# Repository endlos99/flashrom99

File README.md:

FlashROM 99
===========

The *TI 99/4A Flash ROM Cartridge*, or FlashROM 99 for short, is a cartridge
for the TI 99/4A home computer that allows for running ROM cartridge images
stored on an SD card.

The FlashROM 99 supports ROM-only images of up to 32K that use the
write-to-`>60xx` bank switching scheme.  It will not work with programs
using GROMs or CRU-based bank switching.  The cartridge does not require the
Peripheral Expansion Box and runs on both PAL and NTSC consoles.

The project homepage is hosted at [GitHub][1].

FlashROM 99 is released as Open Source Hardware under the
[CERN OHL license][4] and the [GNU GPL license][5].  Both hardware design
files and firmware sources are available on [GitHub][2].

Using the FlashROM 99
---------------------

Using the FlashROM 99 is simple and doesn't require and special hardware or
software.

To begin, copy up to 171 cartridge image files onto an SD or SDHC card.
Switch off the TI 99 and plug in the FlashROM 99, then insert the SD card
into the FlashROM 99.  Switch on the TI 99 and wait until the activity
indicator on the FlashROM 99 is no longer lit.

Press any key to bring up the TI menu screen.  You should see the list of
images found on the SD card.  If the SD card contains more than 8 images, a
`FLASHROM 99` entry is shown instead.  Selecting this entry starts an image
browser where you can page through the list of available images with `,`,
`.`, `SPACE`, and number keys.

Select the image you want to run.  The screen will show a loader animation
while the image loads.  Once the image has been loaded, it will run
automatically.  The SD card is now no longer required and may be removed.

If only one image is found on the SD card, it is loaded immediately without
the need to select it first.

If you want to run a different program from the SD card, reset the TI 99 by
pressing `FCTN-=` and then reset the FlashROM 99 by pushing the reset
button.  If you do not reset the FlashROM 99, the TI menu will show only the
previously selected image.  Alternatively, you can power cycle the console,
which will reset both TI 99 and FlashROM 99.

For detailed usage information please refer to the [FlashROM 99 homepage][1].

Building the FlashROM 99
------------------------

The [GitHub repository][2] contains all hardware design files and software
sources required to build the FlashROM 99.

### Hardware

To assemble the FlashROM 99 you need the following components:

- 1x FlashROM 99 board
- 1x ATmega 8515 (either 8515-16 or 8515L-8)
- 1x 62256 32K SRAM (any speed rating)
- 1x 74HCT377 (LS may also work, but untested)
- 3x 74HCT541 (LS may also work, but untested)
- 6x 100 nF capacitors (e.g., multi-layer ceramic X7R, no electrolytic!)
- 1x 68 Ohm resistor
- 1x 330-470 Ohm resistor (depending on LED used, smaller values will be
     brighter)
- 1x 10 kOhm resistor
- 1x LED (e.g., 5 mm red or yellow)
- 1x micro push button
- 1x SD card module

The FlashROM 99 board was designed with [KiCad][6], a cross platform and
open source electronics design automation suite.  The design files are
stored in `pcb/`.

To simplify the board layout, the design uses an inexpensive SD module that
is readily available online.  Searching for `SD card Arduino` should give
you plenty of hits, including Amazon, ebay, and Pollin.  Make sure to pick a
module that matches the pin-out of the reference module shown below. Note
that the 3.3V input is not used, so any substitutes must be powered by 5V.

You can use any kind of single color LED, but you may have to adjust the 470
Ohm resistor if you choose anything other than red or yellow.

The push button is used to reset the board and will be pushed frequently.
You might choose an angled button if you prefer to push horizontally instead
of vertically.  This will also put less stress on the cart connector.

If the board shows connectors for a 1 nF capacitor next to the 377, do *not*
put this capacitor there, but leave the connectors empty.

When assembling the board make sure to place all ICs properly oriented --
some ICs are upside down!  On the board, the location of pin 1 is indicated
by a small line in the IC outline.  Socketing the ATmega allows for future
software updates.  It is best not to socket the 541s, however, as this will
make inserting the assembled cart into the TI 99 more difficult.

The push button is best soldered to the top of the board so that the bottom
area remains as smooth as possible.  After the button is soldered, put some
insulating tape on its bottom contacts to avoid interference with the SD
module.

Insert the SD module from the bottom and solder either one row of connectors
top so that the metal part of the module is flush with the board.  Some SD
modules have a crooked connector, though, so that a small gap may remain.

If you don't want to build the board yourself feel free to contact the
developer for available sources.

#### Previous Versions

Early versions of the FlashROM 99 used an additional 1 nF capacitor that
resulted in unreliable disk access on some, but not all systems with certain
disk controllers.

Please check to see if the 1 nF capacitor is present on your board.  If so,
simply remove it by desoldering or clipping its wires to improve the
stability of your cart.

If you applied a so-called "disk fix" to your board in the past, you don't
need to undo those changes when removing the capacitor.

### Software

The software for the ATmega 8515 consists of two components.  The `avr/`
folder contains the microcontroller logic for accessing the SD card, filling
the SRAM chip, and controlling the TI bus.

The `ti/` folder contains TI 99 assembly sources for the image menu and the
image browser.  The assembled TMS 9900 machine code is embedded in the
microcontroller code and loaded into RAM during operation.

To build the software, you first need to assemble the menu and browser
program with [`xas99`][3] and convert the generated machine code into C
code:

	$ cd ti/
	$ xas99.py -b -R -I <xdt99>/lib menu.a99
	$ mkmenu.py

Now you can compile the microcontroller code in `avr/`.  The folder contains
a `Makefile` for `avr-gcc` that will make compilation trivial.

	$ cd avr/
	$ make

As an option, you can enable multi-file functionality in the `Makefile`.
This feature, however, will severely extend the scan time for SD cards with
many images.  Only enable multi-file if you plan to use the FlashROM 99 with
no more than about two dozenzs of images per SD card.  To compile with
multi-file, you may have to disable FAT16 support in `avr/lib/pffconf.h` in
case the executable gets too large.

The build yields a `.hex` file that you can flash to the ATmega 8515 using
[`avrdude`][7] or your programmer of choice:

	$ avrdude -p atmega8515 -P /dev/ttyACM0 -c stk500 -U flash:w:flashrom99.hex

Additionally, you need to program the lower fuse bits of the 8515 so that it
runs at 8 MHz:

	$ avrdude -p atmega8515 -P /dev/ttyACM0 -c stk500 -U lfuse:w:0xe4:m

If you're using a different tool chain make sure to set `CKSEL3..0` in the
lower fuse byte to `0100`.  (Note that `0` means "programmed", and `1` means
"unprogrammed").  You can verfify that you're running at the right clock
speed by resetting the FlashROM 99 with no SD card inserted: The LED should
blink about once per second.

Finally, make sure that the bootloader is disabled by checking if higher
fuse bits `BOOTSZ1`, `BOOTSZ0`, and `BOOTRSET` are all set to `1`.  This
should be the default for new 8515s.

In the end, the lower and higher fuse bytes should have values `E4` and
`D9`, respectively.

About the Project
-----------------

The TI 99/4A Flash ROM Cartridge is Open Source Hardware released under the
[CERN OHL license][4], in the hope that TI 99 enthusiasts may find it useful.
Software components are released under the [GNU GPL license][5].

The hardware was designed with the open source electronics design automation
suite [KiCad][6].  The microcontroller code uses a modified version of the
[Petit FatFs][8] library.  Thanks go to Jon Guidry (acadiel) of `hexbus.com`
for designing the original bank switching circuitry for the first TI
multi-carts.

Contributions to both hardware and software are very welcome!  Please email
feedback, support questions, inquiries for parts, and bug reports to the
developer at <r@0x01.de>.  Discussions about the FlashROM 99 happen over at
[AtariAge][9].

[1]: https://endlos99.github.io/flashrom99
[2]: https://github.com/endlos99/flashrom99
[3]: https://endlos99.github.io/xdt99
[4]: http://www.ohwr.org/projects/cernohl/wiki
[5]: http://www.gnu.org/licenses/gpl.html
[6]: http://kicad.org
[7]: http://www.nongnu.org/avrdude/
[8]: http://elm-chan.org/fsw/ff/00index_p.html
[9]: http://atariage.com/forums/topic/250540-flash-rom-cart

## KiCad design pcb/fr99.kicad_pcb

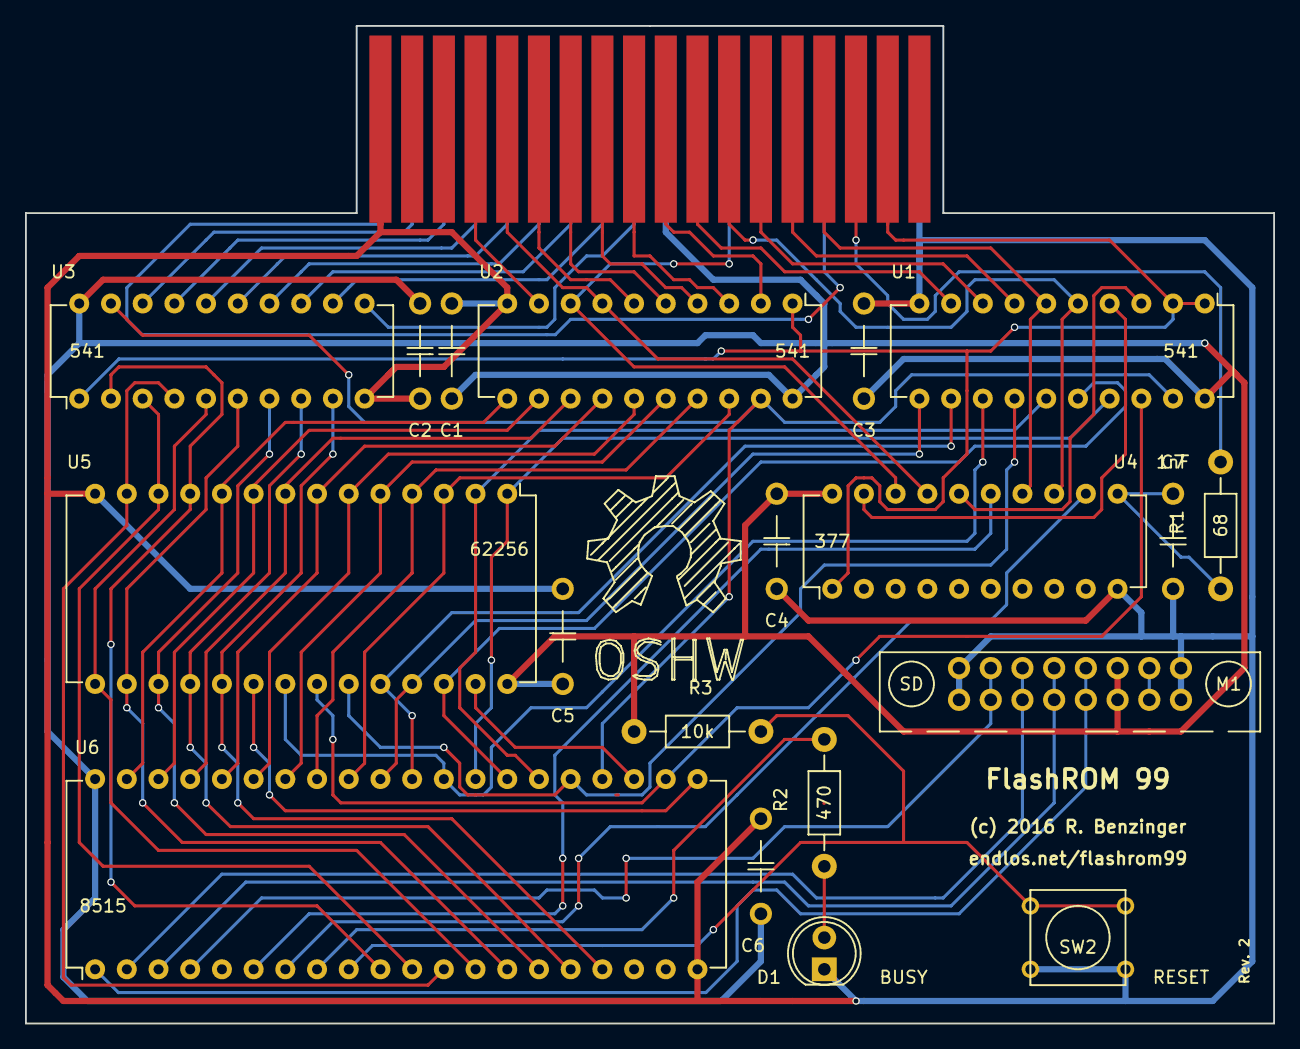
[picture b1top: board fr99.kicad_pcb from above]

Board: 2 copper layers, 100.0 x 79.9 mm, 20 parts (0 on the bottom side), 65 nets.

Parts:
C1, C2, C3, C4, C5, C6: 100nF; C_C
C7: 1nF; C_C
D1: BUSY; LED-5MM
M1: SD; SD_MODULE
P1: CONN_02X18; BUS_CART
R1: 68; Resistor_Horizontal_RM10mm
R2: 470; Resistor_Horizontal_RM10mm
R3: 10k; Resistor_Horizontal_RM10mm
SW2: RESET; SW_PUSH_SMALL
U1, U2, U3: 541; DIP-20_W7.62mm
U4: 377; DIP-20_W7.62mm
U5: 62256; DIP-28_W15.24mm
U6: 8515; DIP-40_W15.24mm

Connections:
+5V: C1.2, C2.2, C3.2, C4.2, C5.2, C6.2, M1.6, P1.19, R3.1, U1.20, U2.20, U3.20, U4.20, U5.28, U6.40
/A0: U2.11, U5.10, U6.39
/A1: U2.12, U5.9, U6.38
/A2: U2.13, U5.8, U6.37
/A3: U2.14, U5.7, U6.36
/A4: U2.15, U5.6, U6.35
/A5: U2.16, U5.5, U6.34
/A6: U2.17, U5.4, U6.33
/A7: U2.18, U5.3, U6.32
/A8: U1.11, U5.25, U6.31
/A9: U1.12, U5.24, U6.30
/A10: U1.13, U5.21, U6.29
/A11: U1.14, U5.23, U6.25
/A12: U1.15, U5.2, U6.26
/A13: U1.16, U5.26, U6.27
/A14: U1.17, U5.1, U6.28
/D0: U3.2, U5.11, U6.10
/D1: U3.3, U5.12, U6.11
/D2: U3.4, U5.13, U6.12
/D3: U3.5, U5.15, U6.13
/D4: U3.6, U5.16, U6.14
/D5: U3.7, U5.17, U6.15
/D6: U3.8, U5.18, U6.16
/D7: U3.9, U5.19, U6.17
BUSE: U1.19, U2.19, U3.19, U6.24
GND: C1.1, C2.1, C3.1, C4.1, C5.1, C6.1, C7.2, D1.1, M1.1, M1.8, P1.2, P1.35, SW2.1, U1.10, U2.10, U3.10, U4.10, U5.14, U6.20
unnamed: C7.1, R1.1, U4.11
unnamed: D1.2, R2.1
unnamed: M1.2, U6.4
unnamed: M1.3, U6.2
unnamed: M1.4, U6.3
unnamed: M1.5, U6.1
unnamed: P1.1, P1.29
unnamed: P1.3, U3.18
unnamed: P1.5, U3.17
unnamed: P1.7, U3.16
unnamed: P1.8, U2.9
unnamed: P1.9, U3.15
unnamed: P1.10, U2.7, U4.17
unnamed: P1.11, U3.14
unnamed: P1.12, U2.6
unnamed: P1.13, U3.13
unnamed: P1.14, U2.5
unnamed: P1.15, U3.12
unnamed: P1.16, U2.4
unnamed: P1.17, U3.11
unnamed: P1.18, U2.3
unnamed: P1.20, U2.2
unnamed: P1.22, U1.9
unnamed: P1.23, U2.8, U4.18
unnamed: P1.24, U1.5, U4.13
unnamed: P1.26, U1.8
unnamed: P1.28, U1.7
unnamed: P1.30, U1.6, U4.14
unnamed: P1.32, R1.2
unnamed: R2.2, U6.8
unnamed: R3.2, SW2.2, U6.9
unnamed: U1.3, U4.16
unnamed: U1.4, U4.19
unnamed: U1.18, U5.22, U6.22
unnamed: U4.12, U6.7
unnamed: U4.15, U6.6
unnamed: U5.20, U6.21
unnamed: U5.27, U6.23
ROMS: P1.34, U1.1, U1.2, U2.1, U3.1, U4.1

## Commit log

2016-05-07 FR99: documentation
2016-05-07 Create gh-pages branch via GitHub
2016-05-16 FR99: initial release of FlashROM 99 v1.0
2016-06-05 PCB: added values to silkscreen
2016-06-07 FR99: updated manual
2016-06-10 FR99: added sample images
2016-06-10 PCB: fixed bank switch (disk access issue)
2016-06-10 FR99: updated documentation
2016-06-12 FR99: clarified disk fix
2016-07-01 FR99: updated fix: no cap
2016-07-11 FR99: fixed typo in README
2016-09-15 FR99: removed obsolete disk fix images
2016-11-06 PCB: added Gerber files
2017-01-18 AVR: added HEX file
2018-04-16 DOC: fix fuse bytes description
2021-11-09 Update README.md
    https://forum.kicad.info/t/warning-avoid-all-links-to-kicad-pcb-org-use-kicad-org/31521

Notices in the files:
pcb/fr99.kicad_pcb:
Copyright (c) 2016 Ralph Benzinger
Released as Open Source Hardware under CERN OHL 1.2 and GNU GPL 3 licenses
(c) 2016 R. Benzinger
